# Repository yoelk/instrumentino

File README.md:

# Instrumentino2
Version "2" of Instrumentino, which needs its own repository because the whole project is rebuilt anew.

Note: Project is still in pre-release development. Current documentation is being maintained on the [Main help page](http:/yoelk.github.io/instrumentino/index.html)

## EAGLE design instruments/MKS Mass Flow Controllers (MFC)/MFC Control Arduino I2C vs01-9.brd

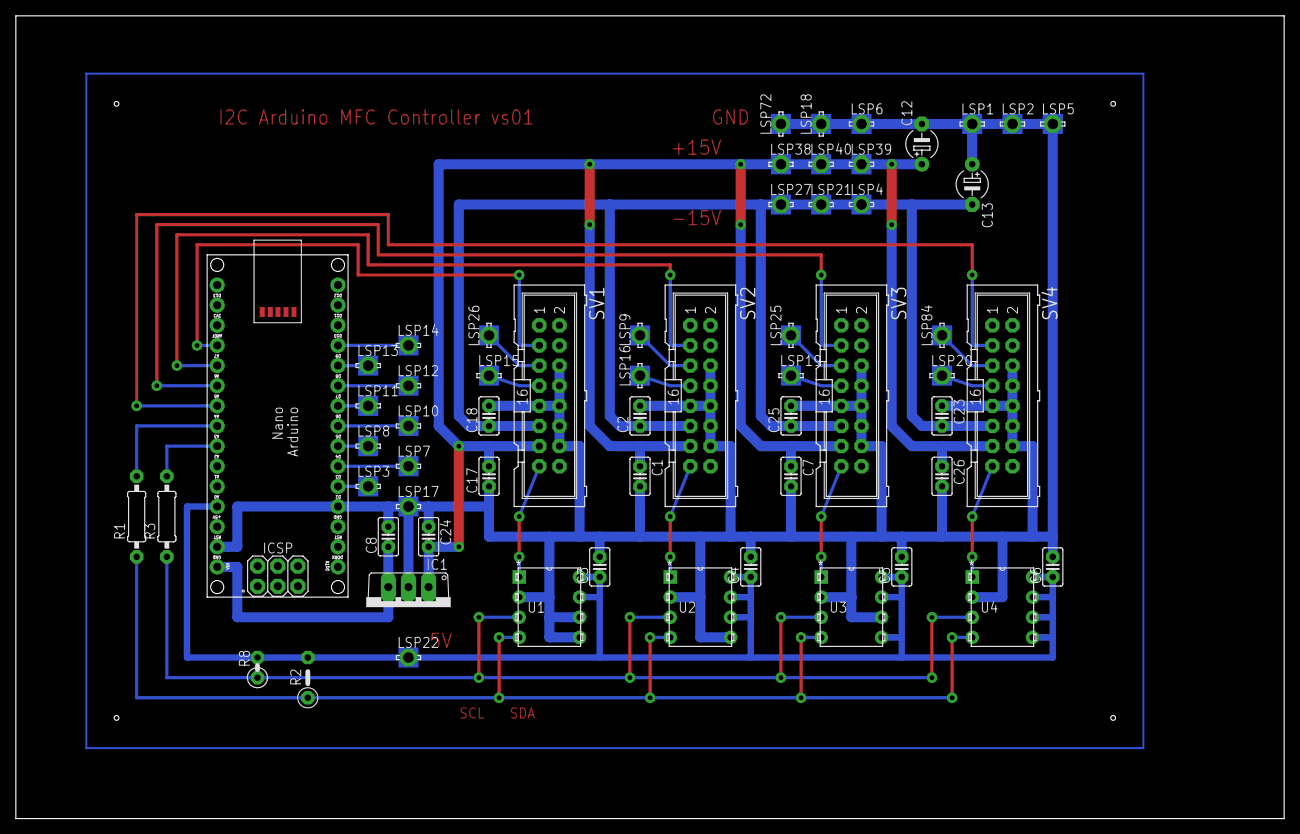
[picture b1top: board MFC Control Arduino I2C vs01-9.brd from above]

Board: 2 copper layers, 159.9 x 101.1 mm, 60 parts (0 on the bottom side), 33 nets.

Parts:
C1, C2, C3, C4, C5, C6, C7, C8, C17, C18, C23, C24, C25, C26: C025-025X050
C12, C13: 10µF; E5-4
IC1: 7812TV; TO220V
LSP1, LSP2, LSP3, LSP4, LSP5, LSP6, LSP7, LSP8, LSP9, LSP10, LSP11, LSP12, LSP13, LSP14, LSP15, LSP16, LSP17, LSP18, LSP19, LSP20, LSP21, LSP22, LSP25, LSP26, LSP27, LSP38, LSP39, LSP40, LSP72, LSP84: LSP13
PCB1: ARDUINO_NANO
R1, R3: 330R; 0207/10
R2: 10k; 0207/5V
R8: 10k; 0207/2V
SV1, SV2, SV3, SV4: ML16
U1, U2, U3, U4: MAX517ACPA+; 21-0043D_8

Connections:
GND: C1.2, C2.2, C3.2, C4.2, C5.2, C6.2, C7.2, C8.2, C12.-, C13.+, C17.1, C18.2, C23.1, C24.1, C25.2, C26.2, IC1.2, LSP1.MP, LSP2.MP, LSP5.MP, LSP6.MP, LSP17.MP, LSP18.MP, LSP72.MP, PCB1.GND, PCB1.GND., SV1.6, SV1.8, SV1.9, SV1.10, SV1.12, SV1.14, SV2.6, SV2.8, SV2.9, SV2.10, SV2.12, SV2.14, SV3.6, SV3.8, SV3.9, SV3.10, SV3.12, SV3.14, SV4.6, SV4.8, SV4.9, SV4.10, SV4.12, SV4.14, U1.2, U1.5, U1.6, U2.2, U2.5, U3.2, U3.6, U4.2
unnamed: LSP3.MP, PCB1.D2
unnamed: LSP7.MP, PCB1.D3
unnamed: LSP8.MP, PCB1.D4
unnamed: PCB1.A0, SV1.3
unnamed: PCB1.A1, SV2.3
unnamed: PCB1.A3, SV4.3
unnamed: PCB1.A2, SV3.3
unnamed: SV2.15, U2.1
unnamed: LSP26.MP, SV1.5
unnamed: LSP9.MP, SV2.5
unnamed: LSP25.MP, SV3.5
unnamed: LSP84.MP, SV4.5
unnamed: PCB1.A4, R1.2
unnamed: LSP10.MP, PCB1.D5
unnamed: SV1.15, U1.1
unnamed: R1.1, R2.1, U1.4, U2.4, U3.4, U4.4
unnamed: SV3.15, U3.1
unnamed: PCB1.A5, R3.2
unnamed: LSP11.MP, PCB1.D6
unnamed: SV4.15, U4.1
unnamed: C3.1, C4.1, C5.1, C6.1, LSP22.MP, PCB1.5V, R2.2, R8.2, U1.7, U1.8, U2.6, U2.7, U2.8, U3.5, U3.7, U3.8, U4.5, U4.6, U4.7, U4.8
unnamed: R3.1, R8.1, U1.3, U2.3, U3.3, U4.3
unnamed: LSP12.MP, PCB1.D7
unnamed: LSP13.MP, PCB1.D8
unnamed: LSP14.MP, PCB1.D9
unnamed: C8.1, IC1.3, PCB1.VIN
unnamed: LSP16.MP, SV2.7
unnamed: LSP15.MP, SV1.7
unnamed: LSP19.MP, SV3.7
unnamed: LSP20.MP, SV4.7
V+: C1.1, C7.1, C12.+, C17.2, C24.2, C26.1, IC1.1, LSP38.MP, LSP39.MP, LSP40.MP, SV1.13, SV2.13, SV3.13, SV4.13
V-: C2.1, C13.-, C18.1, C23.2, C25.1, LSP4.MP, LSP21.MP, LSP27.MP, SV1.11, SV2.11, SV3.11, SV4.11

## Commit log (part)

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2014-07-25 start
2014-07-25 update description and contact details
2014-08-20 Make __init__.py runnable with a simple example
2014-08-20 version 1.01
2014-08-20 Add the controlino to the resource folder
2014-09-09 update contact details
2014-09-09 same
2014-09-23 Add support for UM30_4 Spellman HV module
2014-10-31 Add support for PID controlled variables, using the Arduino PID library which was incorporated into Controlino (http://playground.arduino.cc/Code/PIDLibrary).
    At the moment, the only implemented type is a PID-relay variable, as in
    the following example:
    http://playground.arduino.cc/Code/PIDLibraryRelayOutputExample
2014-10-31 new version 1.05
2014-10-31 put controlino in its own github tree
2014-10-31 add controlino to the same git repository
2014-10-31 test
2014-10-31 add controlino to the instrumentino repository
2014-11-01 add documents
    add documents from the Instrumentino release article’s supplementary
    material
2014-11-16 - add a more elaborate example instrument
    - add a few example instruments in a new folder "instruments"
    - make the log look better. now there is a legend instead of multiple
    Y-axes. Each variable is plotted as a percentage from 0-100, and if the
    value is negative, the trace becomes dashed.
    It's also possible to hide traces from the graph view, using the legend
2014-11-16 - add different line thicknesses to acocmodate a lot of variables.
    - remove an unnecessary print
2014-11-17 Add support for LabSmith sensor manifold (4AM01)
    Also enlarge the communication buffers in controlino
2014-11-17 I don't know why this didn't work before. In this commit I improve the log graph and add a better default example to __init__.py @ instrumentino
2014-11-17 new version - 1.06
2014-11-19 ignore some files
2014-11-19 default value should be 0
    until I find a better way of doing that, like adding a default value
    for each variable. This is probably the way to go.
2014-12-02 - add EMCO high voltage module support - add tuning commands for PID
2014-12-02 like before
2014-12-04 ignore release and build
2014-12-04 fix bug in hardware serial usage
2014-12-07 Add the release article
2014-12-08 minor change
2014-12-08 add some documentation to PyPi
2014-12-08 Add support for more Arduino boards
    And make Controlino more self-explanatory
2014-12-09 trying to use gitignore properly
2014-12-09 cosmetic change in the list controls
2014-12-12 fix a bug in controlino
2014-12-22 add Roland's notes for installation under Windows
2014-12-22 update documentation
2015-01-06 Add a powerpoint presentation about Instrumentino
2015-05-19 add I2C DAC support, LabSmith syringe pressurization, second article
2015-05-22 ignore .mk files
2015-06-16 add remarks to the MFC schematics
2015-06-16 many updates, mainly to the LabSmith interface.
    System configuration files using LabSmith pumps must be revised
2015-06-16 try again
2015-10-30 move instrumentino2 to the instrumentino repository as a develop branch
2015-11-01 Calculate the length field automatically, following an advice in GitHub
    For more details:
    https://github.com/construct/construct/issues/58#issuecomment-151576195
2015-11-02 ignore
2015-11-02 can't seem to ignore these files
2015-11-02 couldn't ignore them either
2015-11-02 them as well
2015-11-02 allow to ignore traces on the graph
2015-11-02 allow using an I2C DAC
2015-11-02 Use threads to have the screen not stuck when long LabSmith operations happen
2015-11-02 clean up
2015-11-02 allow stopping the syringe on the move
2015-11-02 rename back to controlino
2015-11-02 small rename
2015-11-02 rename and add commands
2015-11-02 again
2015-11-02 replace RTC:ZERO with ACQUIRE:START to make it more clear what this command does
2015-11-02 num of blocks can be a single byte. it's enough
2015-11-02 set different DEBUG flags
2015-11-02 try working with several analog inputs
2015-11-02 allow more than one simulation pattern
2015-11-02 Fix bug that didn't let us see more than one channel
2015-11-03 not needed anymore
2015-11-03 make nicer simulation patterns
2015-11-04 give nicer default names
2015-11-04 give a default name
2015-11-04 separate the parts in the variable's screen name
2015-11-04 show all parts
2015-11-04 add translation to variables' units
2015-11-06 update variable values on the screen and create instrumentino.cfg
    move to cfg all of the things everyone needs, like the DEBUG modes.
2015-11-06 Set up the control panel to let the user change variable values
2015-11-07 Added popup confirmation on press of escape key
2015-11-08 Create gh-pages branch via GitHub
2015-11-14 Manually merged v2 gh-pages branch into v1 gh-pages branch. Some updating of the docs.
2015-11-15 Update to clarify between versions
    small changes in text
2015-11-15 remove whitespace
    another formatting issue
2015-11-19 Allow channel types to be more than one character
2015-11-19 move the DEBUG_AUTO_CONNECT properties to cfg.py
2015-11-22 small rename and some comments
2015-11-22 implement writing to digital pins
    Set the pins’ direction at startup, in a new dedicated method
    (do_first_when_online) that is available for all channel classes.
2015-11-22 Skip D0 and D1 because they're in charge of communication
2015-11-23 add egg file
2015-11-23 this shouldn't be here
2015-11-23 Fix a bug related to the lists
    The bug: When only two items are in a list, deleting no.1 will not
    update the remaining item’s number correctly.
    Now it does.
2015-11-23 bug fix relating to folder creation
    The bug was that under windows, “user” folders were created
    unnecessarily.
    It was fixed by using a global variable to remember the initial path
2015-12-09 email
2015-12-18 make the component classes controller-independent
    and make simulation default
2015-12-18 fix small bug
    The path was missing a slash
2016-02-06 Modify the way we check for necessary attributes
    In the new way, they can be passed to the parent class in two ways:
    - By setting the attribute’s value in the child class’s __init__ method
    or in its definition
    - By passing it through kwargs
2016-02-06 pass the attributes another way
2016-02-06 Change id to be different than the attribute holding it
2016-02-06 check if the attribute has a value instead of checking if it was passed in the kwargs
2016-02-19 Give priority to kwargs for getting attributes
2016-02-19 Get all attributes of a certain type
    Use this to automatically identify certain definitions, without the
    necessity of calling add_X() methods.
2016-02-19 make the variable class cover all cases in which we want to show a variable on the screen
2016-02-19 clean up a bit
2016-02-19 define the action class in a new way
2016-02-19 cancel exit confirmation until we get it to work better
2016-02-19 Get a primitive list of actions (only strings at the moment)
2016-02-20 add an action class instead of an instance
    It makes no sense instantiating the Action class, as all of the
    relevant data should come from the user
2016-02-20 save possible action classes
    the instances will be kept in the ListView’s data in the automation view
2016-02-20 Use a custom class to keep the list data
2016-02-20 Added instructions for instalation on gnu/linux
2016-02-21 add link to documents folder
2016-02-21 Update .gitignore to support JetBrains IDEs
    I'm switching over to PyCharm and it creates a few IDE specific files. Applied recommended settings
2016-02-22 Automatically extract data about an instrument
    By looking at the __main__ module and searching its __dict__ for the
    right objects and class definitions.
    Also move get_default_name() to cfg.py, because it belongs there,
    rather than being a static method.
2016-02-23 rearrange the instrument configuration file according to the new way
2016-02-24 Add a list view of actions
    The data in the list is still constant, but the list has some basic
    functionality
2016-02-25 Add the possibility to create default names without the index
2016-02-25 split screens.kv to separate kv files
2016-02-25 Work further on the automation list
    - Make a container for the parameters.
    - Make a class for holding the data for each list item
    - Add a default action for loading action files
2016-02-25 This hack doesn't work anyway. I have to find out why we have this window problem
2016-02-26 add an installation guide
2016-02-26 Move main.py to be in the instrumentino (module __main__.py)
    So now we can import garden libraries the normal way, and change them
    internally if needed.
    There are some quirks in the GUI that I still need to fix
2016-02-26 rename togglebuttonmulti
2016-02-26 don't know what this was doing here, but it didn't let the window be resized
2016-02-26 move libraries to libs
2016-02-26 save libs2 for now, until I'm sure we can throw it
2016-02-26 Always show all of the views on startup
2016-03-20 Update README.md
    Updated to correct URL.
2016-04-05 Add remove functionality
2016-04-06 rename classes and remove useless method
2016-04-06 With the new attribute passing mechanism, I don't need to check kwargs again
    This fixes the recent bug in which I couldn’t see the numbers on the
    screen for analog variables
2016-04-28 update comment
2016-04-28 start forking between screen variables and communication variables
    screen variables don’t need to serialise their data, so they don’t need
    the whole percentage mess.
2016-04-29 finish adding the duration variable
2016-04-29 Revert "Merge pull request #33 from yoelk/order-variables-hierarchy"
2016-05-02 still need to connect the widget to the changing data of a variable (input and output)
2016-05-04 continue
    I saw that kvlang doesn’t work on list widgets that don’t have
    sub-widgets, so I implemented everything in python instead.
    Still not working:
    - digital variables’ spinner doesn’t open when clicked on
    - action choosing spinner doesn’t do anything and I don’t know how to
    get it to call a function when it’s pressed
2016-05-25 some changes
2016-05-25 move stuff
2016-05-25 add controlino as a submodule and update Pewatron
2016-06-20 on Linux systems the Arduinos don't have a '.' after 'tty'
    So now in OS X we’ll have a lot more things to choose from but at least
    in Linux it would work
2016-06-21 remove controlino so I can add it later as a nested repository
2016-06-21 moved controlino to v2
2016-06-23 Add linux install details and example to original documentation
2016-06-23 update documentation and raise version to 1.32
    Thanks Ludo
2016-06-24 Add SPI support and make the example include SPI and I2C
2016-06-25 forgot to declare the parent class
2016-06-25 And make sure we inherit from object
2017-02-18 The type of the analog value was int by default and not float. So I had to make sure float is used in the conversion
2017-02-18 Damn it. This took a while to realize. Only properties that are defined in the class level (instead in __init__) create instances for each created object. Other objects defined this way are STATIC!!!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
2017-02-18 Check if "variable" is there
2017-02-18 found another resouce for learning about Kivy
2017-02-19 prettier print
2017-02-19 bugfix. h and m have to be ints for this to work
2017-02-27 I think it's ok to init name out of __init__ because it was defined in the baseclass
2017-02-27 bug fix. I was changing the list while looping on it and it created problems. Now I run on a copy of it.
2017-02-27 add filebrowser
2017-02-27 Redo the popups from scratch
2017-02-27 redo popups from scratch
2017-02-27 implement loading/saving files
2017-04-08 start using pandas for data acquisition. Each input channel gets its own pandas DataFrame with DateTime objects as the index. It uses more memory but is more comfortable than the current situation
2017-04-11 it works now, but still no graph
2017-04-17 ohhhhh, too many changes at once! I wanted to use pandas, and then I started having errors from using the construct library, so I decided to upgrade to the new version, that should be used with Pytho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
